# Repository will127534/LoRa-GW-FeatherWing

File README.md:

# LoRa Gateway FeatherWing

## Description
This is a LoRa Gateway board designed for FeatherWing ecosystem, based on Semtech SX1303 Digital Baseband Chip and Ublox EVA-7M GPS module. Board schematic is largely based on the SX1303 reference design, and this board is designed for 915Mhz operation.

**This Design is still in development process, please use with caution**  
Current issue is that I need to tune the RF impendence because there is an additional SX1261 for LBT hook up to the rx path.

**MCU software is also in development process**  
You can find it here https://github.com/will127534/SX1302_Arduino_Library

## FeatherWing Connection usage
SX1303 uses the SPI bus an two GPIO (CS and Reset on D5 and D6) on the FeatherWing to communicate with host MCU, and GPS module uses the UART pins and a GPIO for pulse-per-second output on A5.

## Design Tool
KiCad v5.99 is used to design the board, and JLCPCB to manufactured the board.

I'm pretty noob about the KiCad stuff, so any feedback is welcome.

## Parts sourcing
I sourced most parts from Mouser, here is the parts list:
https://www.mouser.com/ProjectManager/ProjectDetail.aspx?AccessID=11549c8008

Note: SMA connector is not included, because it is related to the board thickness your are using, I'm using 1mm 4 layer pcb, and I can't find the connector on Mouser.

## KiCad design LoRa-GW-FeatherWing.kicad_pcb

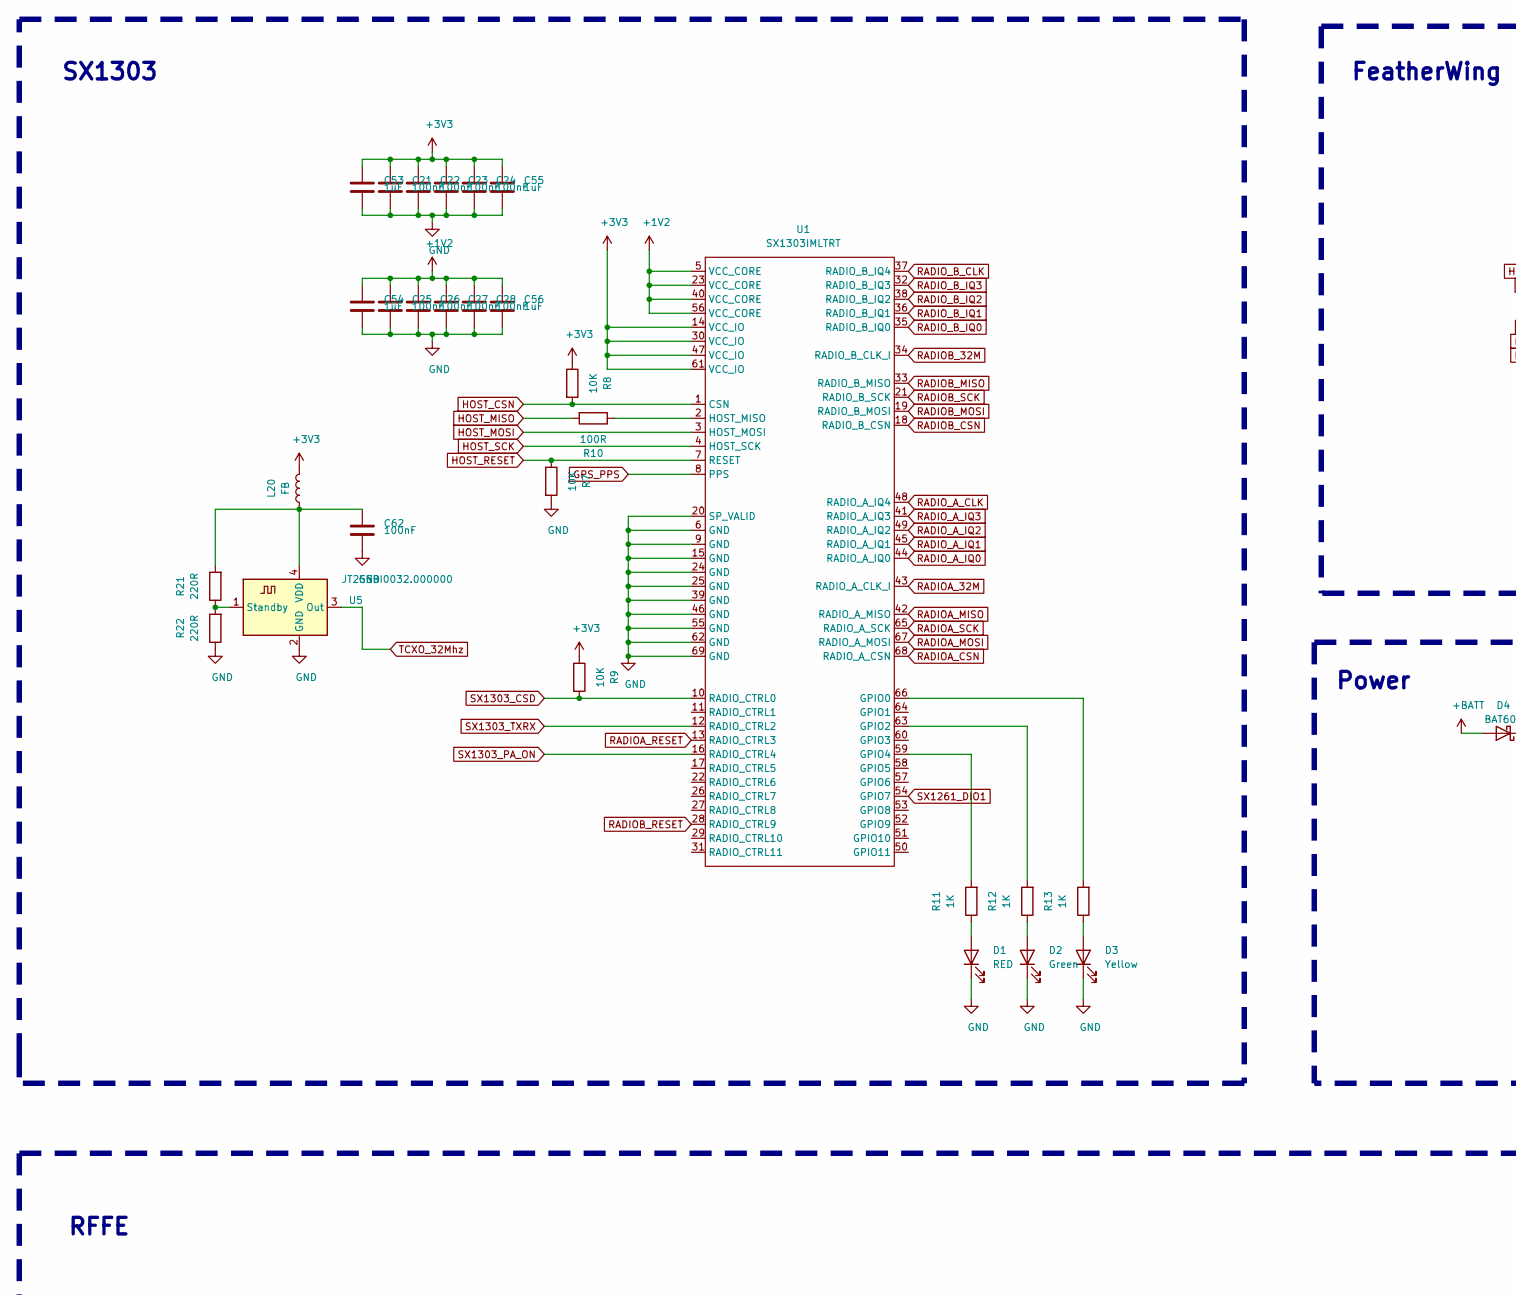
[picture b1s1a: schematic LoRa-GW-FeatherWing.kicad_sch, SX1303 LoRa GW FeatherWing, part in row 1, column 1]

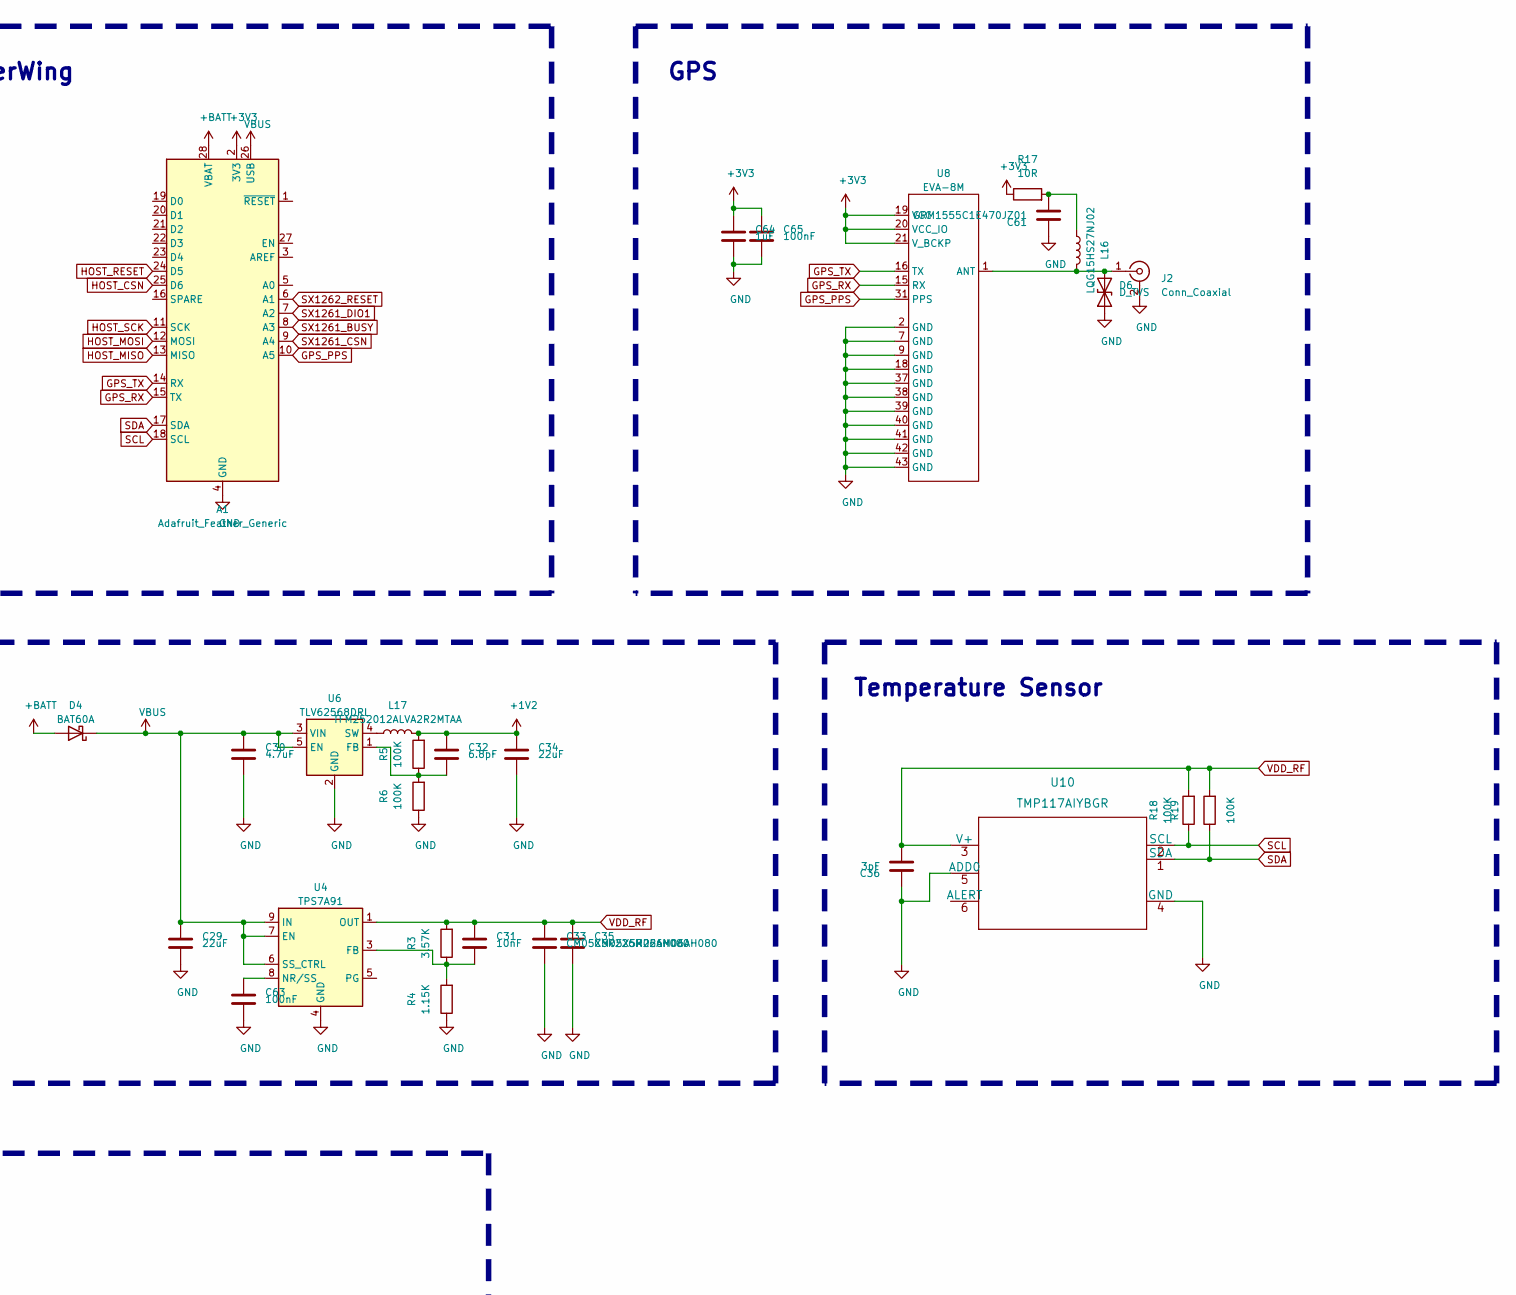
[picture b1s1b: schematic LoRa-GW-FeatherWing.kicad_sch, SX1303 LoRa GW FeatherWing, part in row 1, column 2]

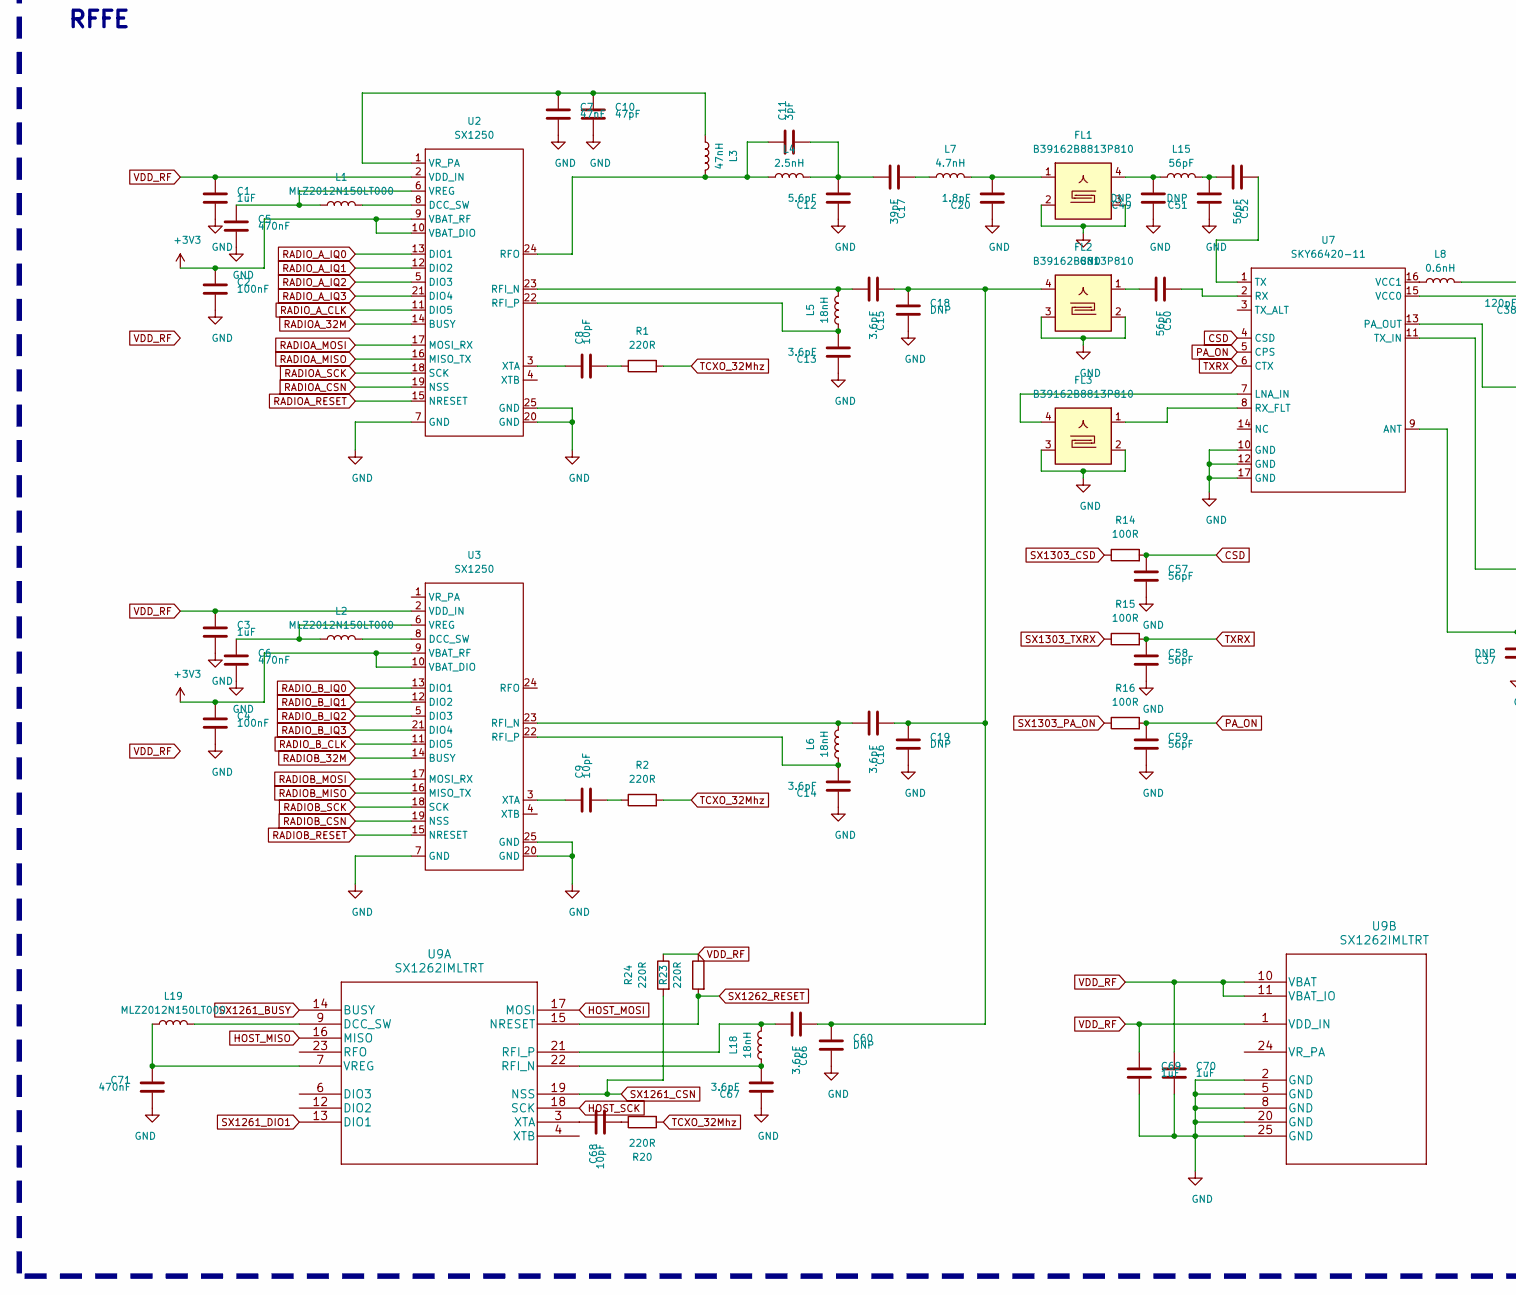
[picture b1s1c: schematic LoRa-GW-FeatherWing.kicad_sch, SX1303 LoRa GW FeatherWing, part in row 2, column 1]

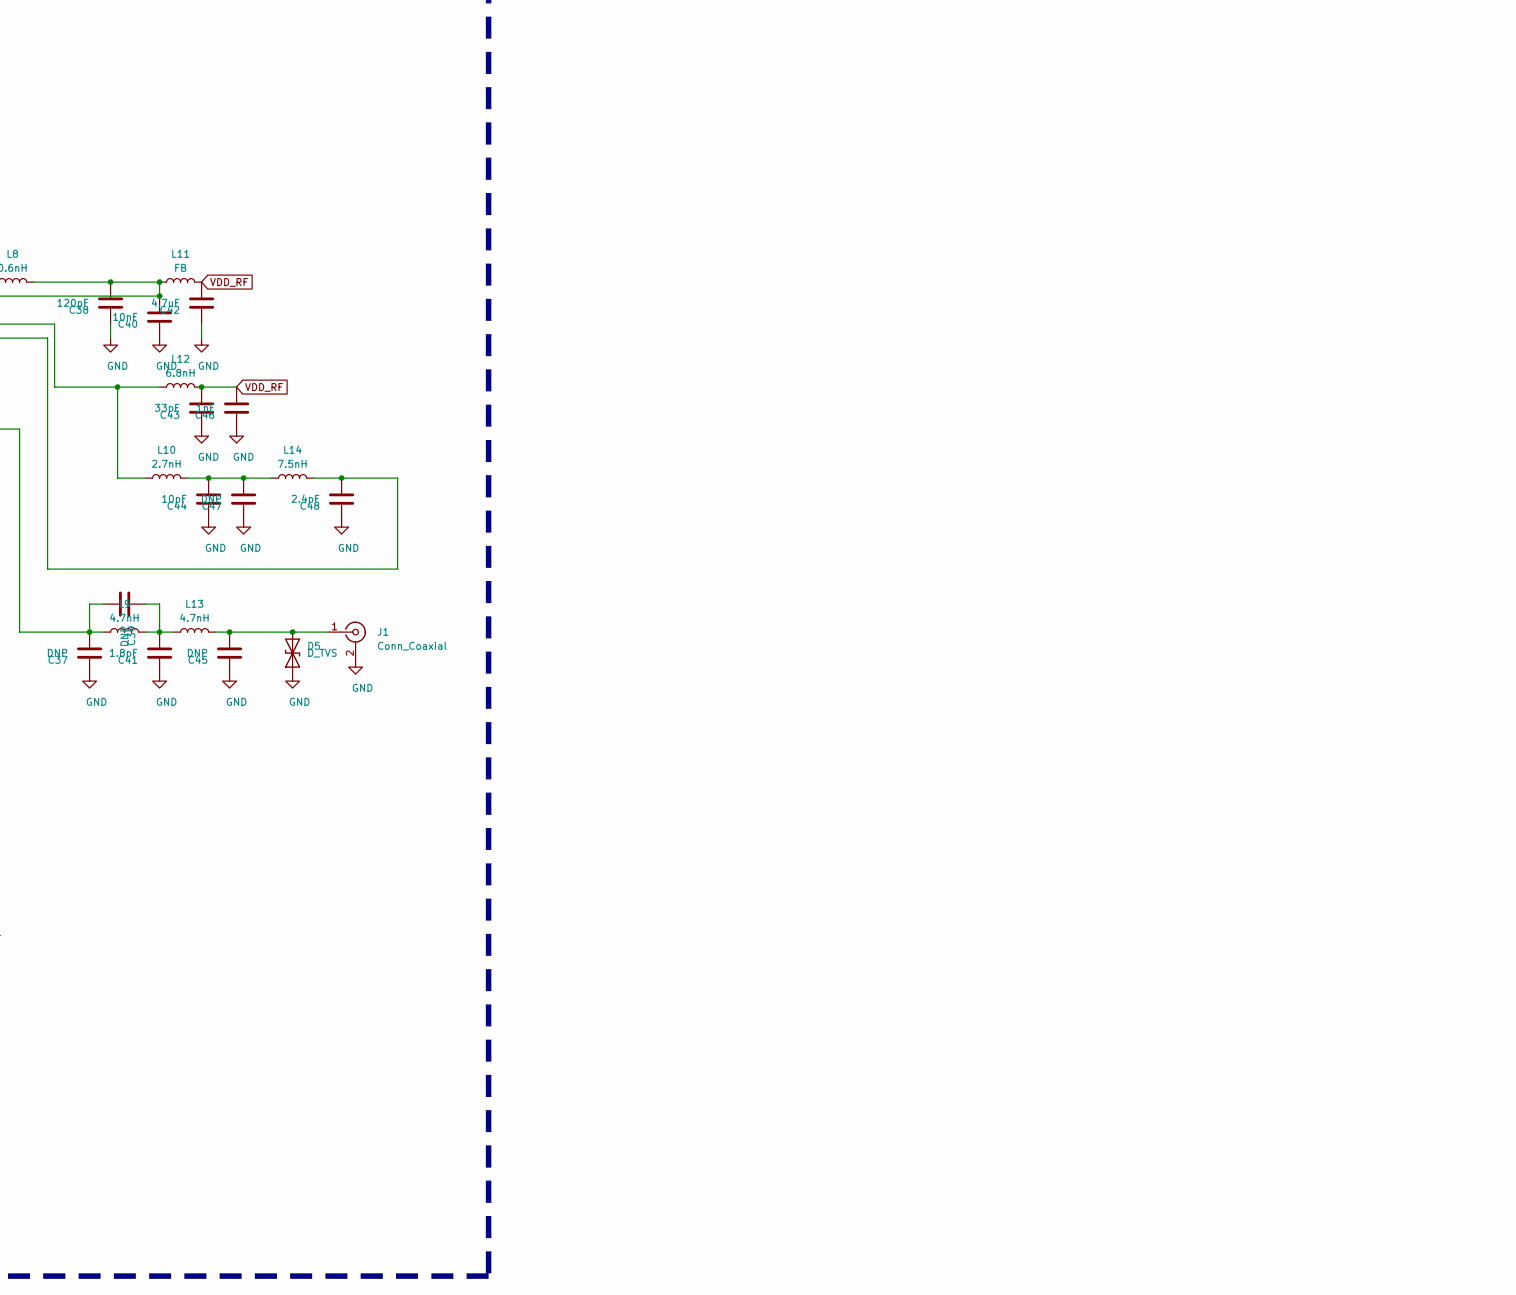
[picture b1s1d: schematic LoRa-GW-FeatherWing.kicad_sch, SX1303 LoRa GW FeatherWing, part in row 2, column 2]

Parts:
A1: Adafruit_Feather_Generic; Adafruit_Feather
C1, C3, C64, C69, C70: 1uF; C_0402_1005Metric
C2, C4, C65: 100nF; C_0402_1005Metric
C5, C6, C71: 470nF; C_0402_1005Metric
C7: 47nF; C_0402_1005Metric
C8, C9, C44, C68: 10pF; C_0201_0603Metric
C10: 47pF; C_0402_1005Metric
C11, C36: 3pF; C_0201_0603Metric
C12: 5.6pF; C_0201_0603Metric
C13, C14, C15, C16, C66, C67: 3.6pF; C_0201_0603Metric
C17: 39pF; C_0201_0603Metric
C18, C19, C37, C39, C45, C47, C49, C51, C60: DNP; C_0201_0603Metric
C20, C41: 1.8pF; C_0201_0603Metric
C21, C22, C23, C24, C25, C26, C27, C28, C62, C63: 100nF; C_0201_0603Metric
C29: 22uF; C_0402_1005Metric
C30, C42: 4.7uF; C_0402_1005Metric
C31: 10nF; C_0402_1005Metric
C32: 6.8pF; C_0402_1005Metric
C33, C35: CM05X5R226M06AH080; C_0603_1608Metric
C34: 22uF; C_0603_1608Metric
C38: 120pF; C_0201_0603Metric
C40: 10nF; C_0201_0603Metric
C43: 33pF; C_0201_0603Metric
C46: 1nF; C_0201_0603Metric
C48: 2.4pF; C_0201_0603Metric
C50, C52, C57, C58, C59: 56pF; C_0201_0603Metric
C53, C54, C55, C56: 1uF; C_0201_0603Metric
C61: GRM1555C1E470JZ01; C_0402_1005Metric
D1: RED; LED_0603_1608Metric
D2: Green; LED_0603_1608Metric
D3: Yellow; LED_0603_1608Metric
D4: BAT60A; D_SOD-323
D5, D6: D_TVS; D_0402_1005Metric
FL1, FL2, FL3: B39162B8813P810; Filter_1109-5_1.1x0.9mm
J1: Conn_Coaxial; SMA_Samtec_SMA-J-P-X-ST-EM1_EdgeMount
J2: Conn_Coaxial; U.FL_Hirose_U.FL-R-SMT-1_Vertical
L1, L2, L19: MLZ2012N150LT000; L_0805_2012Metric
L3: 47nH; L_0201_0603Metric
L4: 2.5nH; L_0201_0603Metric
L5, L6, L18: 18nH; L_0201_0603Metric
L7, L9, L13: 4.7nH; L_0201_0603Metric
L8: 0.6nH; L_0201_0603Metric
L10: 2.7nH; L_0201_0603Metric
L11, L20: FB; L_0201_0603Metric
L12: 6.8nH; L_0201_0603Metric
L14: 7.5nH; L_0201_0603Metric
L15: 56pF; L_0201_0603Metric
L16: LQG15HS27NJ02; L_0402_1005Metric
L17: TFM252012ALVA2R2MTAA; L_1008_2520Metric
R1, R2, R20, R21, R22, R23, R24: 220R; R_0201_0603Metric
R3: 3.57K; R_0402_1005Metric
R4: 1.15K; R_0402_1005Metric
R5, R6: 100K; R_0402_1005Metric
R7, R8, R9: 10K; R_0201_0603Metric
R10, R14, R15, R16: 100R; R_0201_0603Metric
R11, R12, R13: 1K; R_0402_1005Metric
R17: 10R; R_0402_1005Metric
R18, R19: 100K; R_0201_0603Metric
U1: SX1303IMLTRT; SX1302IMLTRT
U2, U3: SX1250; HVQFN-24-1EP_4x4mm_P0.5mm_EP2.5x2.5mm
U4: TPS7A91; Texas_S-PDSO-N10_EP1.2x2mm
U5: JT255BI0032.000000; Oscillator_SMD_Abracon_ASDMB-4Pin_2.5x2.0mm
U6: TLV62568DRL; SOT-563
U7: SKY66420-11; QFN-16-1EP_3x3mm_P0.5mm_EP1.75x1.75mm
U8: EVA-8M
U9: SX1262IMLTRT
U10: TMP117AIYBGR

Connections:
+1V2: C25.1, C26.1, C27.1, C28.1, C32.1, C34.1, C54.1, C56.1, L17.2, R5.2, U1.5 (VCC_CORE), U1.23 (VCC_CORE), U1.40 (VCC_CORE), U1.56 (VCC_CORE)
+3V3: A1.2 (3V3), C2.1, C4.1, C21.1, C22.1, C23.1, C24.1, C53.1, C55.1, C64.1, C65.1, L20.2, R8.1, R9.1, R17.1, U1.14 (VCC_IO), U1.30 (VCC_IO), U1.47 (VCC_IO), U1.61 (VCC_IO), U2.9 (VBAT_RF), U2.10 (VBAT_DIO), U3.9 (VBAT_RF), U3.10 (VBAT_DIO), U8.19 (VCC), U8.20 (VCC_IO), U8.21 (V_BCKP)
+BATT: A1.28 (VBAT), D4.2 (A)
CSD: C57.1, R14.2, U7.4 (CSD)
GND: A1.4 (GND), C1.2, C2.2, C3.2, C4.2, C5.2, C6.2, C7.2, C10.2, C12.1, C13.1, C14.1, C18.2, C19.2, C20.1, C21.2, C22.2, C23.2, C24.2, C25.2, C26.2, C27.2, C28.2, C29.2, C30.2, C33.2, C34.2, C35.2, C36.1, C37.1, C38.1, C40.1, C41.1, C42.1, C43.1, C44.1, C45.1, C46.1, C47.1, C48.1, C49.1, C51.1, C53.2, C54.2, C55.2, C56.2, C57.2, C58.2, C59.2, C60.2, C61.1, C62.2, C63.2, C64.2, C65.2, C67.1, C69.2, C70.2, C71.2, D1.1 (K), D2.1 (K), D3.1 (K), D5.1 (A1), D6.1 (A1), FL1.2, FL1.3, FL1.5, FL2.2, FL2.3, FL2.5, FL3.2, FL3.3, FL3.5, J1.2 (Ext), J2.2 (Ext), R4.1, R6.1, R7.2, R22.1, U1.6 (GND), U1.9 (GND), U1.15 (GND), U1.20 (SP_VALID), U1.24 (GND), U1.25 (GND), U1.39 (GND), U1.46 (GND), U1.55 (GND), U1.62 (GND), U1.69 (GND), U2.7 (GND), U2.20 (GND), U2.25 (GND), U3.7 (GND), U3.20 (GND), U3.25 (GND), U4.4 (GND), U4.11 (GND), U5.2 (GND), U6.2 (GND), U7.10 (GND), U7.12 (GND), U7.17 (GND), U8.2 (GND), U8.7 (GND), U8.9 (GND), U8.18 (GND), U8.37 (GND), U8.38 (GND), U8.39 (GND), U8.40 (GND), U8.41 (GND), U8.42 (GND), U8.43 (GND), U9.2 (GND), U9.5 (GND), U9.8 (GND), U9.20 (GND), U9.25 (GND), U10.4 (GND), U10.5 (ADD0)
GPS_PPS: A1.10 (A5), U1.8 (PPS), U8.31 (PPS)
GPS_RX: A1.15 (TX), U8.15 (RX)
GPS_TX: A1.14 (RX), U8.16 (TX)
HOST_CSN: A1.25 (D6), R8.2, U1.1 (CSN)
HOST_MISO: A1.13 (MISO), R10.2, U9.16 (MISO)
HOST_MOSI: A1.12 (MOSI), U1.3 (HOST_MOSI), U9.17 (MOSI)
HOST_RESET: A1.24 (D5), R7.1, U1.7 (RESET)
HOST_SCK: A1.11 (SCK), U1.4 (HOST_SCK), U9.18 (SCK)
unnamed: C5.1, L1.1, U2.6 (VREG)
unnamed: C6.1, L2.1, U3.6 (VREG)
unnamed: C8.1, U2.3 (XTA)
unnamed: C8.2, R1.1
unnamed: C9.1, U3.3 (XTA)
unnamed: C9.2, R2.1
unnamed: C7.1, C10.1, L3.1, U2.1 (VR_PA)
unnamed: C11.1, L3.2, L4.1, U2.24 (RFO)
unnamed: C11.2, C12.2, C17.2, L4.2
unnamed: C13.2, L5.1, U2.22 (RFI_P)
unnamed: C14.2, L6.1, U3.22 (RFI_P)
unnamed: C15.1, C16.1, C18.1, C19.1, C60.1, C66.1, FL2.4
unnamed: C15.2, L5.2, U2.23 (RFI_N)
unnamed: C16.2, L6.2, U3.23 (RFI_N)
unnamed: C17.1, L7.1
unnamed: C20.2, FL1.1, L7.2
unnamed: C31.2, R3.1, R4.2, U4.3 (FB)
unnamed: C32.2, R5.1, R6.2, U6.1 (FB)
unnamed: C37.2, C39.2, L9.1, U7.9 (ANT)
unnamed: C38.2, C40.2, L8.2, L11.1, U7.15 (VCC0)
unnamed: C39.1, C41.2, L9.2, L13.1
unnamed: C44.2, C47.2, L10.2, L14.1
unnamed: C45.2, D5.2 (A2), J1.1 (In), L13.2
unnamed: C48.2, L14.2, U7.11 (TX_IN)
unnamed: C49.2, FL1.4, L15.1
unnamed: C50.1, U7.2 (RX)
unnamed: C50.2, FL2.1
unnamed: C51.2, C52.2, L15.2
unnamed: C52.1, U7.1 (TX)
unnamed: C61.2, L16.1, R17.2
unnamed: C62.1, L20.1, R21.2, U5.4 (VDD)
unnamed: C63.1, U4.8 (NR/SS)
unnamed: C66.2, L18.2, U9.21 (RFI_P)
unnamed: C67.2, L18.1, U9.22 (RFI_N)
unnamed: C68.1, U9.3 (XTA)
unnamed: C68.2, R20.1
unnamed: C71.1, L19.2, U9.7 (VREG)
unnamed: D1.2 (A), R11.1
unnamed: D2.2 (A), R12.1
unnamed: D3.2 (A), R13.1
unnamed: D6.2 (A2), J2.1 (In), L16.2, U8.1 (ANT)
unnamed: FL3.1, U7.8 (RX_FLT)
unnamed: FL3.4, U7.7 (LNA_IN)
unnamed: L1.2, U2.8 (DCC_SW)
unnamed: L2.2, U3.8 (DCC_SW)
unnamed: L8.1, U7.16 (VCC1)
unnamed: L10.1, L12.1, U7.13 (PA_OUT)
unnamed: L17.1, U6.4 (SW)
unnamed: L19.1, U9.9 (DCC_SW)
unnamed: R10.1, U1.2 (HOST_MISO)
unnamed: R11.2, U1.59 (GPIO4)
unnamed: R12.2, U1.63 (GPIO2)
unnamed: R13.2, U1.66 (GPIO0)
unnamed: R21.1, R22.2, U5.1 (Standby)
PA_ON: C59.1, R16.2, U7.5 (CPS)
RADIOA_32M: U1.43 (RADIO_A_CLK_I), U2.14 (BUSY)
RADIOA_CSN: U1.68 (RADIO_A_CSN), U2.19 (NSS)
RADIOA_MISO: U1.42 (RADIO_A_MISO), U2.16 (MISO_TX)
RADIOA_MOSI: U1.67 (RADIO_A_MOSI), U2.17 (MOSI_RX)
RADIOA_RESET: U1.13 (RADIO_CTRL3), U2.15 (NRESET)
RADIOA_SCK: U1.65 (RADIO_A_SCK), U2.18 (SCK)
RADIOB_32M: U1.34 (RADIO_B_CLK_I), U3.14 (BUSY)
RADIOB_CSN: U1.18 (RADIO_B_CSN), U3.19 (NSS)
RADIOB_MISO: U1.33 (RADIO_B_MISO), U3.16 (MISO_TX)
RADIOB_MOSI: U1.19 (RADIO_B_MOSI), U3.17 (MOSI_RX)
RADIOB_RESET: U1.28 (RADIO_CTRL9), U3.15 (NRESET)
RADIOB_SCK: U1.21 (RADIO_B_SCK), U3.18 (SCK)
RADIO_A_CLK: U1.48 (RADIO_A_IQ4), U2.11 (DIO5)
RADIO_A_IQ0: U1.44 (RADIO_A_IQ0), U2.13 (DIO1)
RADIO_A_IQ1: U1.45 (RADIO_A_IQ1), U2.12 (DIO2)
RADIO_A_IQ2: U1.49 (RADIO_A_IQ2), U2.5 (DIO3)
RADIO_A_IQ3: U1.41 (RADIO_A_IQ3), U2.21 (DIO4)
RADIO_B_CLK: U1.37 (RADIO_B_IQ4), U3.11 (DIO5)
RADIO_B_IQ0: U1.35 (RADIO_B_IQ0), U3.13 (DIO1)
RADIO_B_IQ1: U1.36 (RADIO_B_IQ1), U3.12 (DIO2)
RADIO_B_IQ2: U1.38 (RADIO_B_IQ2), U3.5 (DIO3)
RADIO_B_IQ3: U1.32 (RADIO_B_IQ3), U3.21 (DIO4)
SCL: A1.18 (SCL), R18.1, U10.2 (SCL)
SDA: A1.17 (SDA), R19.1, U10.1 (SDA)
SX1261_BUSY: A1.8 (A3), U9.14 (BUSY)
SX1261_CSN: A1.9 (A4), R24.2, U9.19 (NSS)
SX1261_DIO1: A1.7 (A2), U1.54 (GPIO7), U9.13 (DIO1)
SX1262_RESET: A1.6 (A1), R23.2, U9.15 (NRESET)
SX1303_CSD: R9.2, R14.1, U1.10 (RADIO_CTRL0)
SX1303_PA_ON: R16.1, U1.16 (RADIO_CTRL4)
SX1303_TXRX: R15.1, U1.12 (RADIO_CTRL2)
TCXO_32Mhz: R1.2, R2.2, R20.2, U5.3 (Out)
TXRX: C58.1, R15.2, U7.6 (CTX)
VBUS: A1.26 (USB), C29.1, C30.1, D4.1 (K), U4.6 (SS_CTRL), U4.7 (EN), U4.9 (IN), U4.10 (IN), U6.3 (VIN), U6.5 (EN)
VDD_RF: C1.1, C3.1, C31.1, C33.1, C35.1, C36.2, C42.2, C43.2, C46.2, C69.1, C70.1, L11.2, L12.2, R3.2, R18.2, R19.2, R23.1, R24.1, U2.2 (VDD_IN), U3.2 (VDD_IN), U4.1 (OUT), U4.2 (OUT), U9.1 (VDD_IN), U9.10 (VBAT), U9.11 (VBAT_IO), U10.3 (V+)

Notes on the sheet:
RFFE
SX1303
Power
FeatherWing
GPS
Temperature Sensor

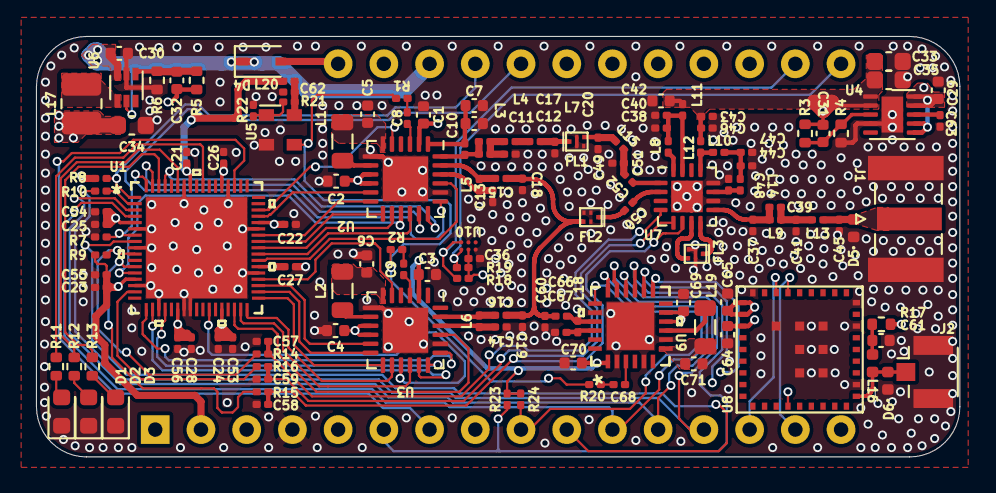
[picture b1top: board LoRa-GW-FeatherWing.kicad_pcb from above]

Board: 4 copper layers, 51.3 x 23.4 mm, 137 parts (0 on the bottom side), 103 nets.

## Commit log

2021-02-28 Init
2021-03-01 Fixing GPS TX RX pin flipped issue
2021-03-01 add dril file
2021-03-02 Update License to CERN Open Hardware License
    Submitting this project to OSHW and found out that MIT licence is not a thing, lol.
2021-03-02 Updating Licence
2021-03-02 Place drill file under gerber
2021-03-02 Adding CC BY-SA 4.0
2021-07-05 Adding SX1261 for LBT

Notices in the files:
LoRa-GW-FeatherWing.kicad_sch:
Licensed under CERN-OHL-S v2
parts and their libraries:
Copyright 2016 Accelerated Designs. All rights reserved.
